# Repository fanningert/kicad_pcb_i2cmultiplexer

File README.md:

# I²C Multiplexer

Simple PCB based on TCA9548APWR. Castellated holes with secondary pin header holes are added, for direct PCB soldering. Secondary pin header holes are placed in a matrix of 2,54 mm (100 mils).

## Features

* Solder pads for I²C address
* Solder pads for I²C Pull-Up Resistor

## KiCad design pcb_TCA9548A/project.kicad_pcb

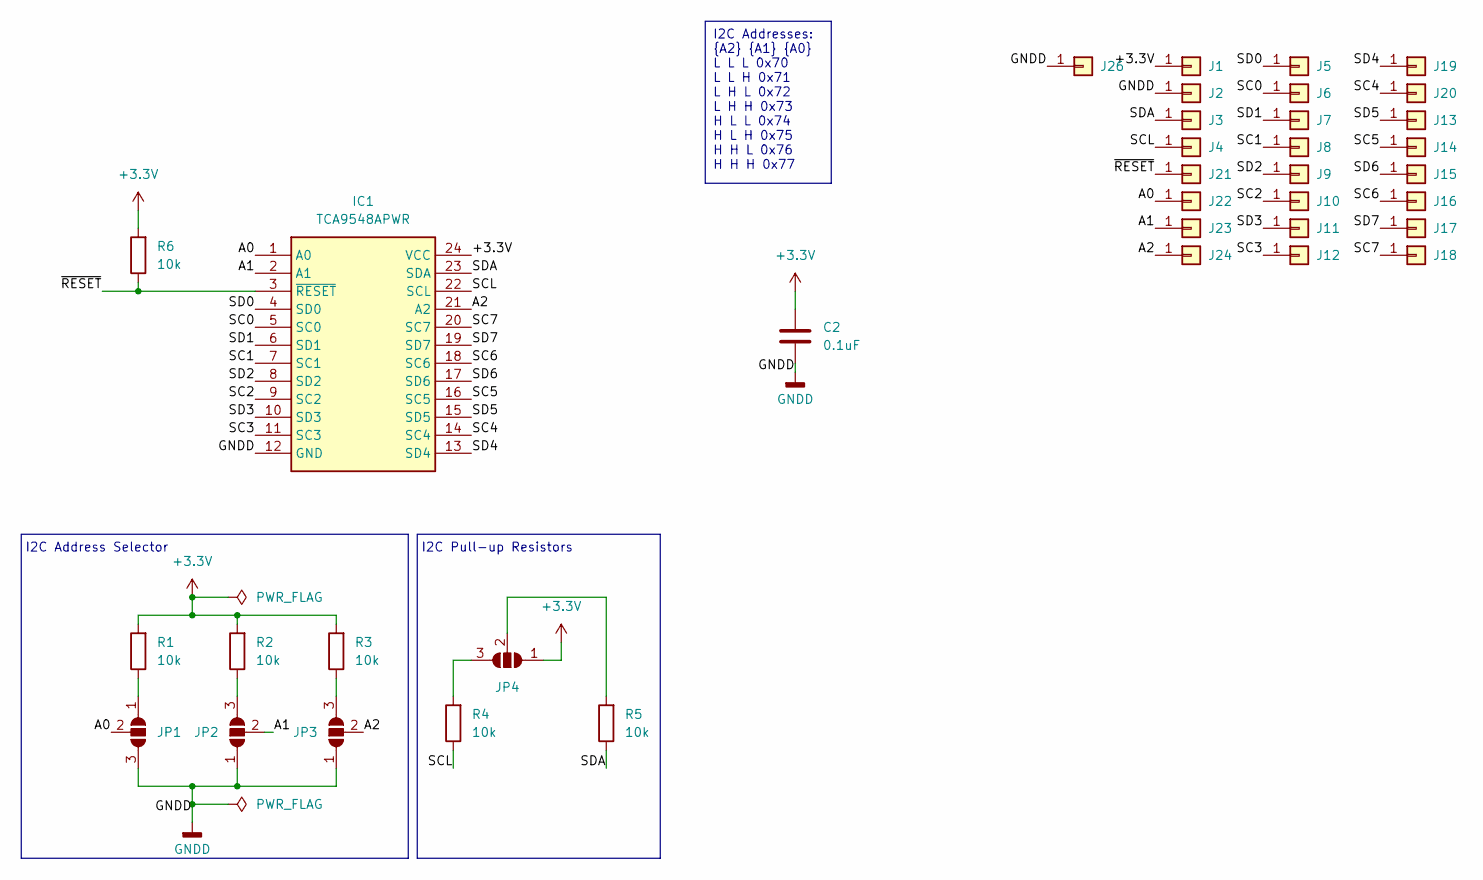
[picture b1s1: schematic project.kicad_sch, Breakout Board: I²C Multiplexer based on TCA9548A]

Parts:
C2: 0.1uF; C_0402_1005Metric_Pad0.74x0.62mm_HandSolder
IC1: TCA9548APWR; SOP65P640X120-24N; Mouser Part Number 595-TCA9548APWR
J1, J2, J3, J4, J5, J6, J7, J8, J9, J10, J11, J12, J13, J14, J15, J16, J17, J18, J19, J20, J21, J22, J23, J24, J26: Castellated_Hole02
JP1, JP2, JP3, JP4: SolderJumper_3_Open; SolderJumper-3_P1.3mm_Open_RoundedPad1.0x1.5mm
R1, R2, R3, R4, R5, R6: 10k; R_0402_1005Metric_Pad0.72x0.64mm_HandSolder

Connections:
+3.3V: C2.1, IC1.24 (VCC), J1.1, JP4.1 (A), R1.2, R2.2, R3.2, R6.2
/A0: IC1.1 (A0), J22.1, JP1.2 (C)
/A1: IC1.2 (A1), J23.1, JP2.2 (C)
/A2: IC1.21 (A2), J24.1, JP3.2 (C)
/SC0: IC1.5 (SC0), J6.1
/SC1: IC1.7 (SC1), J8.1
/SC2: IC1.9 (SC2), J10.1
/SC3: IC1.11 (SC3), J12.1
/SC4: IC1.14 (SC4), J20.1
/SC5: IC1.16 (SC5), J14.1
/SC6: IC1.18 (SC6), J16.1
/SC7: IC1.20 (SC7), J18.1
/SCL: IC1.22 (SCL), J4.1, R4.1
/SD0: IC1.4 (SD0), J5.1
/SD1: IC1.6 (SD1), J7.1
/SD2: IC1.8 (SD2), J9.1
/SD3: IC1.10 (SD3), J11.1
/SD4: IC1.13 (SD4), J19.1
/SD5: IC1.15 (SD5), J13.1
/SD6: IC1.17 (SD6), J15.1
/SD7: IC1.19 (SD7), J17.1
/SDA: IC1.23 (SDA), J3.1, R5.1
/~RESET: IC1.3 (~RESET), J21.1, R6.1
GNDD: C2.2, IC1.12 (GND), J2.1, J26.1, JP1.3 (B), JP2.1 (A), JP3.1 (A)
unnamed: JP1.1 (A), R1.1
unnamed: JP2.3 (B), R2.1
unnamed: JP3.3 (B), R3.1
unnamed: JP4.3 (B), R4.2
unnamed: JP4.2 (C), R5.2

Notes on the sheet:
I2C Addresses: {A2} {A1} {A0} L L L 0x70 L L H 0x71 L H L 0x72 L H H 0x73 H L L 0x74 H L H 0x75 H H L 0x76 H H H 0x77
I2C Pull-up Resistors
I2C Address Selector

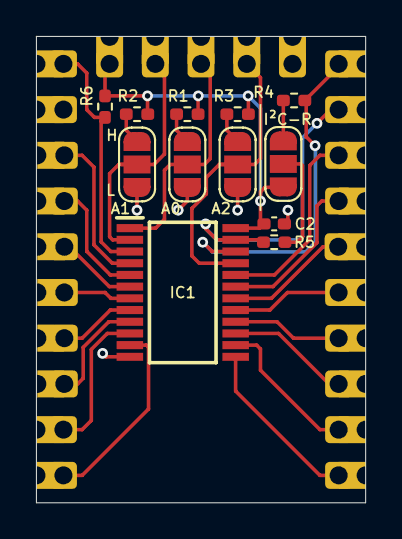
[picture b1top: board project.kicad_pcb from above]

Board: 2 copper layers, 18.3 x 25.9 mm, 38 parts (1 on the bottom side), 29 nets.

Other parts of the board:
QR*****: https://github.com/fanningert/kicad_pcb_i2cmultip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; //github.com/fanningert/kicad_pcb_i2cmultiplexer

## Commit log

2024-06-02 Correct bug in README
2024-06-04 Remove connector on own side
2024-06-04 Remove qrcode from bom
2024-06-09 Add panelize
2024-06-09 Edit panelize config
2024-06-09 Add revision number to PCB
2024-06-09 Update assets
